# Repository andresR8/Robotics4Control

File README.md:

# Robotics4Control
A mini-sized robot for investigation in robotics and control systems
more info at: http://www.coffeebrain.org/wiki/index.php?title=Robotics_4_Control

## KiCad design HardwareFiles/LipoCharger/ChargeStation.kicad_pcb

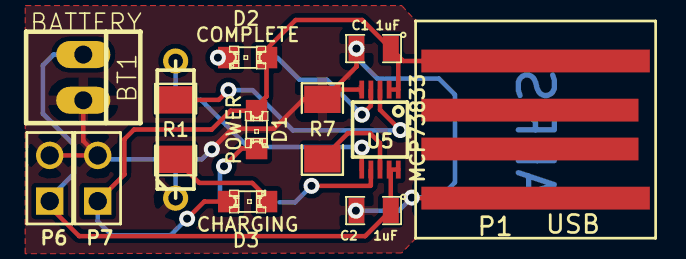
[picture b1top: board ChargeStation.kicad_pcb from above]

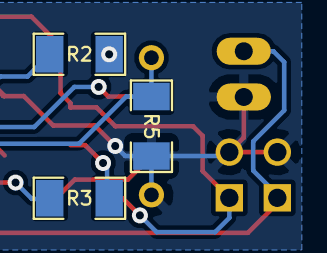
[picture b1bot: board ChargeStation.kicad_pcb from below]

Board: 2 copper layers, 16 parts (3 on the bottom side), 11 nets.

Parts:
BT1: BATTERY; PINHEAD1-2
C1, C2: 1uF; SM0805
D1: POWER; LED-0805
D2: COMPLETE; LED-0805
D3: CHARGING; LED-0805
P1: USB; USB_A_SMD
P6: BATT; PIN_ARRAY_2X1
P7: POWER; PIN_ARRAY_2X1
R1, R2, R3: 470; SM1206
R5: 5K; SM1206
R7: 10K; SM1206
R8: R3
U5: MCP73833; MSOP10-0.5

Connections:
/PROG: R5.2, R8.2, U5.6
GND: BT1.2, C1.2, C2.2, P1.4, P6.2, P7.2, R5.1, R7.1, R8.1, U5.5
unnamed: D2.2, R2.1
unnamed: D1.2, R3.1
unnamed: D3.2, R1.1
unnamed: R3.2, U5.7
unnamed: R1.2, U5.3
unnamed: R2.2, U5.4
unnamed: R7.2, U5.8
unnamed: BT1.1, C2.1, P6.1, U5.9, U5.10
VCC: C1.1, D1.1, D2.1, D3.1, P1.1, P7.1, U5.1, U5.2

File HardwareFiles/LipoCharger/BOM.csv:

Id;Designator;Package;Quantity;Designation;Manufacturer;Manufacturer ID;Mouser ID;Digikey ID
1;R2,R1,R3;SM1206;3;470;Yageo;RC1206FR-07470RL;603-RC1206FR-07470RL;311-470FRCT-ND
2;R5;SM1206;1;5K;Vishay / Dale;ESR18EZPF502;71-CRCW1206-47.5K-E3;541-47.5KFCT-ND
3;R7;SM1206;1;10K;ROHM Semiconductor;CRCW120647K5FKEA;755-ESR18EZPF1002;RHM10.0KAFTR-ND
4;C1,C2;SM0805;2;1uF;Vishay / Vitramon;VJ0805Y105KXQTW1BC;71-CRCW1206-47.5K-E3;490-1691-1-ND
5;BT1;PINHEAD1-2;1;BATTERY;TE Connectivity AMP Connectors;640456-2;"571-6404562
";A1921-ND
6;P6;PIN_ARRAY_2X1;1;BATT;TE Connectivity AMP Connectors;640456-2;"571-6404562
";A1921-ND
7;U5;MSOP10-0.5;1;MCP73833;Microchip;MCP73833-AMI/UN;579-MCP73833-AMI/UN;MCP73833-AMI/UN-ND
8;D1;LED-0805;1;POWER;Kingbright;AP2012EC;604-AP2012EC;AP2012EC-ND
9;D2;LED-0805;1;COMPLETE;Kingbright;AP2012EC;604-AP2012EC;AP2012EC-ND
10;D3;LED-0805;1;CHARGING;Kingbright;AP2012EC;604-AP2012EC;AP2012EC-ND
11;P7;PIN_ARRAY_2X1;1;POWER;TE Connectivity AMP Connectors;640456-2;"571-6404562
";A1921-ND

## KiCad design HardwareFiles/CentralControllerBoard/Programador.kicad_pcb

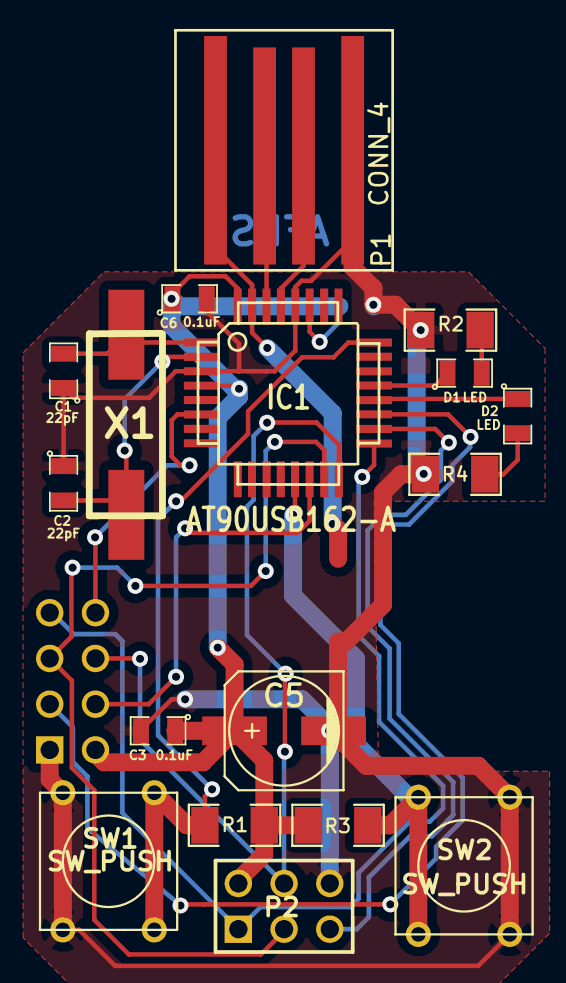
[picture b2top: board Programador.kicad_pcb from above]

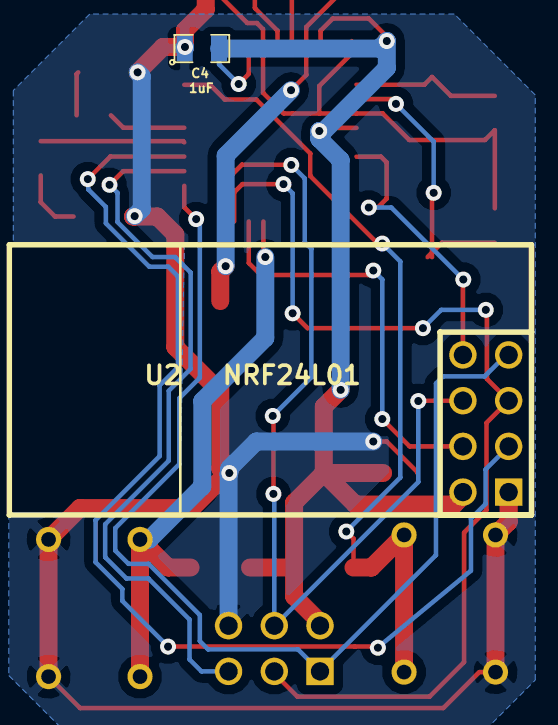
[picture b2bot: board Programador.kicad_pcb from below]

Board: 2 copper layers, 19 parts (2 on the bottom side), 20 nets.

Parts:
C1, C2: 22pF; SM0805
C3, C6: 0.1uF; SM0805
C4: 1uF; SM0805
C5: 10uF; c_elec_6.3x5.3
D1, D2: LED; SM0805
IC1: AT90USB162-A; TQFP32
P1: CONN_4; USB_A_SMD
P2: CONN_3X2; pin_array_3x2
R1, R3: 10k; SM1206
R2, R4: 430; SM1206
SW1, SW2: SW_PUSH; SW_PUSH_SMALL
U2   NRF24L01: NRF24L01; Nrf24l01
X1: crystals

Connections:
+5V: IC1.31, P1.1
/CE: IC1.19, U2 NRF24L01.3
/D+: IC1.29, P1.3
/D-: IC1.30, P1.2
/INT0: IC1.6, U2 NRF24L01.8
/MISO: IC1.17, P2.1, U2 NRF24L01.7
/MOSI: IC1.16, P2.4, U2 NRF24L01.6
/SCK: IC1.15, P2.3, U2 NRF24L01.5
/TARGET_RESET: IC1.18, P2.5
/~SS: IC1.14, U2 NRF24L01.4
GND: C1.1, C2.1, C3.2, C4.1, C5.2, C6.2, IC1.3, IC1.28, P1.4, P2.6, R2.2, R4.2, SW1.1, SW2.2, U2 NRF24L01.1
unnamed: D2.2, R4.1
unnamed: D2.1, IC1.20
unnamed: C2.2, IC1.2, X1.1
unnamed: C1.2, IC1.1, X1.2
unnamed: D1.2, R2.1
unnamed: D1.1, IC1.21
unnamed: IC1.24, R1.2, SW1.2
unnamed: IC1.13, R3.2, SW2.1
VCC: C3.1, C4.2, C5.1, C6.1, IC1.4, IC1.27, IC1.32, P2.2, R1.1, R3.1, U2 NRF24L01.2

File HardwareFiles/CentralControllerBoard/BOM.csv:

Id;Designator;Package;Quantity;Designation;Manufacturer;Manufacturer ID;Mouser ID;Digikey ID
1;IC1;TQFP32;1;AT90USB162-A;Atmel;AT90USB162-16AU;556-A90USB162-16AU;AT90USB162-16AU-ND
2;SW2,SW1;SW_PUSH_SMALL;2;SW_PUSH;TE Connectivity;FSM4JH;506-FSM4JH;450-1650-ND
3;R1,R3;SM1206;2;10K;ROHM Semiconductor;ESR18EZPF1002;755-ESR18EZPF1002;RHM10.0KAFTR-ND
4;R2,R4;SM1206;2;430;Yageo;RC1206JR-07430RL;603-RC1206JR-07430RL;311-430ERCT-ND
5;C2,C1;SM0805;2;22pF;Wurth Electronics;8.85012E+11;710-885012007012;732-7816-1-ND
6;D1,D2;SM0805;2;LED;Kingbright;AP2012EC;604-AP2012EC;AP2012EC-ND
7;C6,C3;SM0805;2;0.1uF;Yageo;CC0805ZRY5V9BB104;603-CC805ZRY5V9BB104;311-1361-1-ND
8;C4;SM0805;1;1uF;Vishay / Vitramon;VJ0805Y105KXQTW1BC;77-VJ0805Y105KXQTBC;490-1691-1-ND
9;P2;pin_array_3x2;1;CONN_3X2;Sullins Connector Solutions;PPTC032LFBN-RC;571-215309-3;
10;U2   NRF24L01;Nrf24l01;1;NRF24L01;NRF24L01;Nordic Semiconductor;http://amzn.com/B00O9O868G;
11;X1;crystals;1;16MHz;ECS Inc.;ECS-160-20-5PX-TR;520-CSM1600-20-X;XC1282CT-ND
12;C5;c_elec_6.3x5.3;1;10uF;Wurth Electronics Inc;8.75E+11;710-875105240001;732-6401-1-ND

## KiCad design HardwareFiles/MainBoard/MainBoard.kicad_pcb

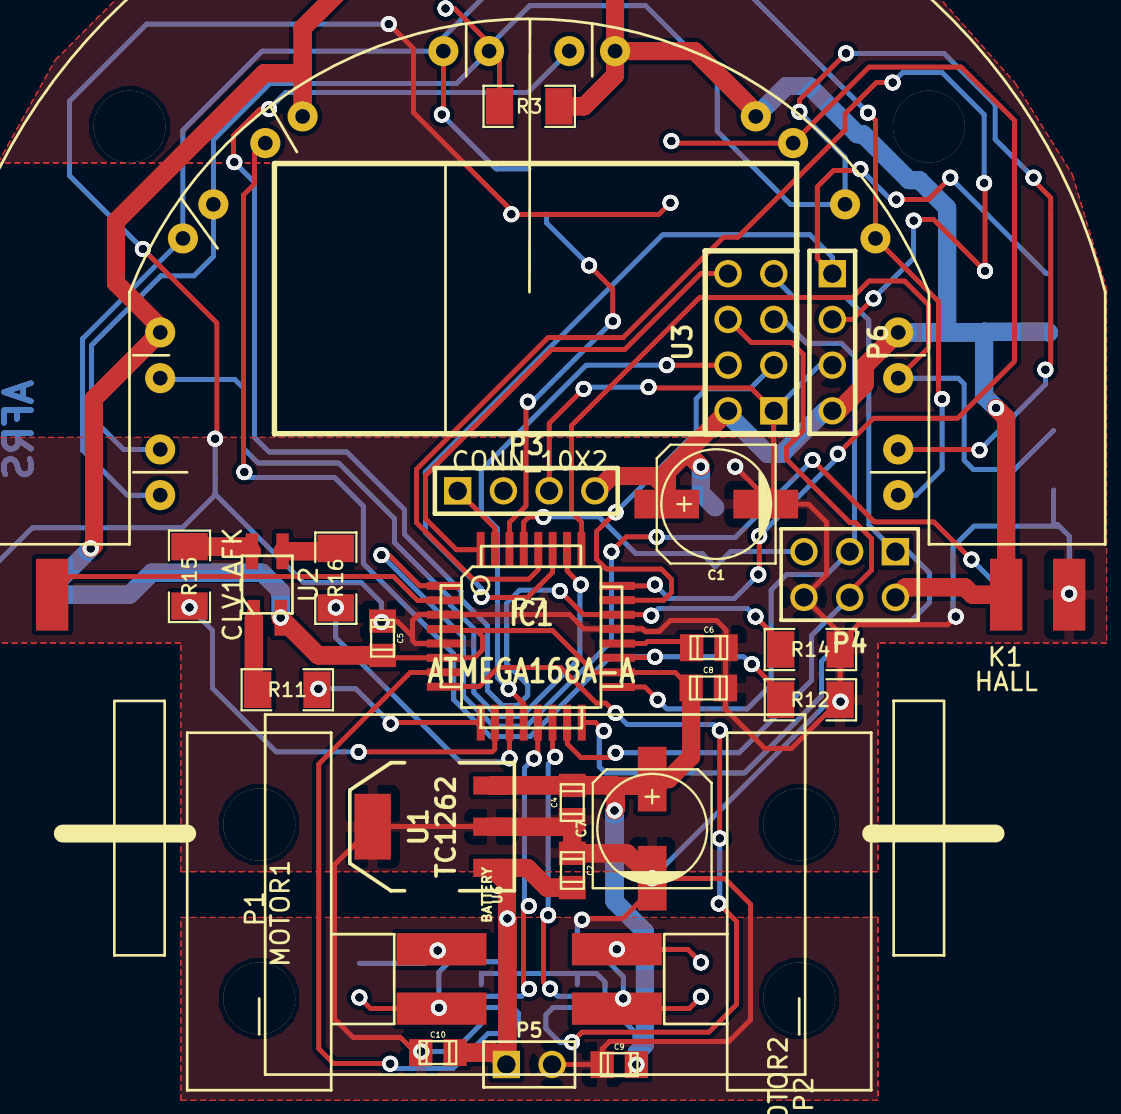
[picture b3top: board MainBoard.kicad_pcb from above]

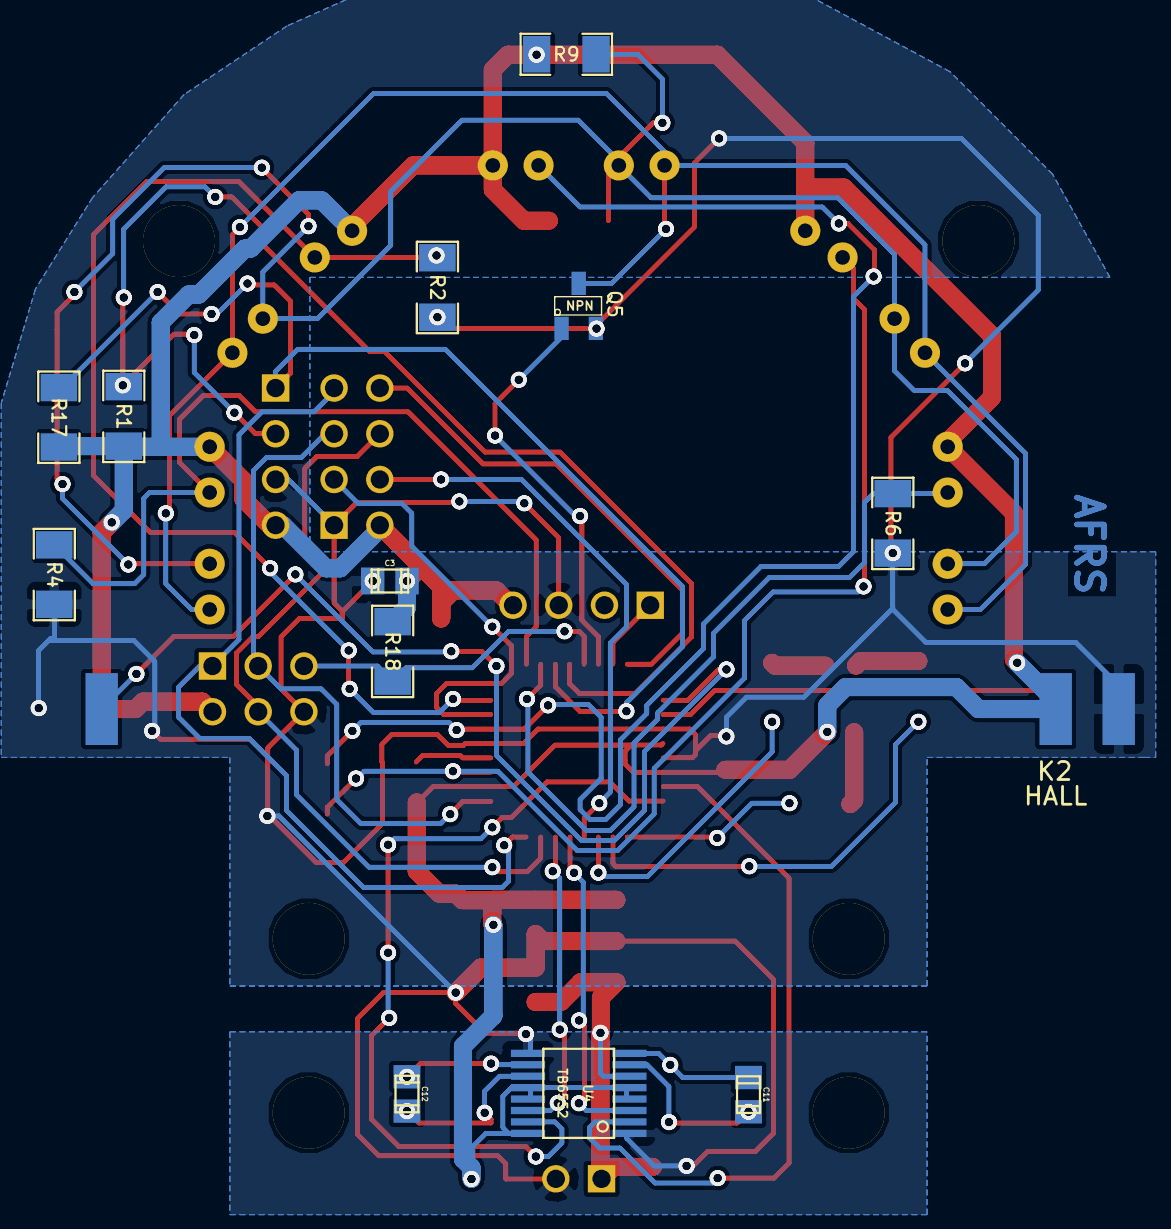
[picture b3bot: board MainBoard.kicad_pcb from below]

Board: 2 copper layers, 41 parts (13 on the bottom side), 38 nets.

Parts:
C1, C7: 10uF; c_elec_6.3x5.3
C2, C4: 1uF; c_0805
C3, C5, C8, C9, C10, C11, C12: 0.1uF; c_0805
C6: 100nF; c_0805
IC1: ATMEGA168A-A; TQFP32
K1, K2: HALL
P1: MOTOR1; MotorLeft
P2: MOTOR2; MotorRight
P3: BT; PIN_ARRAY_4x1
P4: AVRSPI; pin_array_3x2
P5: BATT; PIN_ARRAY_2X1
P6: I2C; PIN_ARRAY_4x1
P7: CONN_10X2; IR_Sensors
Q5: NPN; SOT23_MOD
R1, R17, R18: 10K; SM1206
R2, R4, R6, R12, R14: 1.5K; SM1206
R3, R9: 33; SM1206
R11, R15, R16: 430; SM1206
U1: TC1262; SOT223
U2: CLV1AFK; LEDRGB
U3: NRF24L01; Nrf24l01
U4: TB6552; ssop_16
U6: BATTERY; Battery3x2

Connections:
+3.3V: C1.1, C3.1, C4.1, C5.1, C7.1, C8.2, C9.1, IC1.4, IC1.6, IC1.18, K1.1, K2.1, P3.4, P4.2, P6.4, P7.2, P7.4, P7.6, P7.8, P7.10, R1.2, R3.1, R9.1, R17.2, R18.1, U1.3, U2.2, U3.2, U4.4, U4.5, U4.12, U4.13, U4.16
/ADC1: IC1.24, P7.1, R2.1
/ADC2: IC1.25, P7.3, R4.1
/ADC3: IC1.26, P7.5, R6.1
/ADC6: IC1.19, P7.7, R12.1
/ADC7: IC1.22, P7.9, R14.2
/AO1: C11.1, P1.2, U4.7
/AO2: C11.2, P1.1, U4.8
/BLUE: IC1.11, R16.2
/BO1: C12.1, P2.2, U4.11
/BO2: C12.2, P2.1, U4.10
/CE: IC1.23, U3.3
/GREEN: IC1.10, R15.2
/INT0: IC1.32, U3.8
/M1: IC1.7, U4.2
/M2: IC1.8, U4.15
/MISO: IC1.16, P4.1, U3.7
/MOSI: IC1.15, P4.4, U3.6
/OC1A: IC1.13, U4.3
/OC1B: IC1.14, U4.14
/PCINT19: IC1.1, K1.3
/PCINT20: IC1.2, K2.3
/PD0: IC1.30, Q5.1
/RED: IC1.9, R11.1
/RESET: IC1.29, P4.5, R18.2
/SCK: IC1.17, P4.3, U3.5
/SCL: IC1.28, P6.2, R1.1
/SDA: IC1.27, P6.1, R17.1
/TX: IC1.31, P3.1
/~SS: IC1.12, U3.4
AGND: C1.2, C2.2, C3.2, C4.2, C5.2, C6.1, C7.2, C8.1, C9.2, C10.2, IC1.3, IC1.5, IC1.21, K1.2, K2.2, P3.3, P4.6, P5.2, P6.3, Q5.2, R2.2, R4.2, R6.2, R12.2, R14.1, U1.2, U1.4, U3.1, U4.1, U4.9
unnamed: P7.11, P7.13, P7.15, P7.17, P7.19, Q5.3
unnamed: P7.12, P7.14, P7.16, P7.18, P7.20, R3.2, R9.2
unnamed: R11.2, U2.1
unnamed: R16.1, U2.3
unnamed: R15.1, U2.4
unnamed: C6.2, IC1.20
VCC: C2.1, C10.1, P5.1, U1.1, U4.6

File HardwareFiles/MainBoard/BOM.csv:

Id;Designator;Package;Quantity;Designation;Manufacturer;Manufacturer Part Number;Mouser Part Number;Digikey Part Number
1;P7;IR_Sensors;5;CONN_10X2; Osram Opto Semiconductor;SFH 4545;720-SFH4545;475-2919-ND
1;P8;IR_Sensors/ Phototransistors;5;CONN_10X2;Vishay Semiconductors ;TEFT4300;782-TEFT4300;751-1041-ND
3;Q5;SOT23_MOD;1;NPN;ON Semiconductor;MMBT3904LT3G;863-MMBT2222ALT1G;MMBT2222ALT1GOSCT-ND
4;U4;ssop_16;1;TB6552;Toshiba;TB6552;757-TB6552FNGC8EL;TB6552FNGC8ELCT-ND
5;U2;LEDRGB;1;CLV1AFK;Cree, Inc.;CLV1A-FKB-CHMKPEHBB7A363;941-V1AFKBCHMKPEH7A3;CLV1A-FKB-CK1N1G1BB7R4S3CT-ND
6;R3,R9;SM1206;2;33;ROHM Semiconductor;ESR18EZPJ330;755-ESR18EZPJ330;RHM33ITR-ND
7;R18,R1,R17;SM1206;3;10K;ROHM Semiconductor;ESR18EZPF1002;755-ESR18EZPF1002;RHM10.0KAFTR-ND
8;IC1;TQFP32;1;ATMEGA168A-A;Atmel;ATMEGA168A-AU;556-ATMEGA168A-AU;ATMEGA168A-AU-ND
9;C2,C4;c_0805;2;1uF;Vishay / Vitramon;VJ0805Y105KXQTW1BC;77-VJ0805Y105KXQTBC;490-1691-1-ND
10;C8,C9,C10,C5,C12,C3,C11,C6;c_0805;7;0.1uF;Yageo;CC0805ZRY5V9BB104;603-CC805ZRY5V9BB104;311-1361-1-ND
12;C1,C7;c_elec_6.3x5.3;2;10uF;Wurth Electronics Inc;875105240001;710-875105240001;732-6401-1-ND
13;P1,P2;Motor;2;MOTOR1,MOTOR2;;;;
14;P5;PIN_ARRAY_2X1;1;BATT;;;;
15;P4;pin_array_3x2;1;AVRSPI;Sullins Connector Solutions;PPTC032LFBN-RC;571-215309-3;S7071-ND
16;P3;PIN_ARRAY_4x1;1;BT;Harwin Inc.;M20-7820446;855-M20-7820446;952-1792-ND
17;R2,R4,R12,R14,R6;SM1206;5;1.5K;Yageo;RC1206JR-071K5L;603-RC1206JR-071K5L;311-1.5KERCT-ND
18;R11,R15,R16;SM1206;3;430;Yageo;RC1206FR-07430RL;603-RC1206FR-07430RL;311-430FRCT-ND
19;U1;SOT223;1;TC1262;Microchip Technology;TC1262-3.3VDBTR;579-TC1262-3.3VDBTR;TC1262-3.3VDBCT-ND
21;U3;Nrf24l01;1;NRF24L01;Nordic Semiconductor;;http://amzn.com/B00O9O868G;
22;P6;PIN_ARRAY_4x1;1;I2C;Harwin Inc.;M20-7820446;855-M20-7820446;952-1792-ND

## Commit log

2016-05-07 3D Printed parts
2016-05-07 Central Controller electronic board design
2016-05-07 Lipo Charger electronic board design
2016-05-07 Robot Main Board design
2016-05-07 Robot Software sketch
2016-05-07 AVRISP MKII Programmer
2016-05-07 USB to NRFL24L01 Project
2016-05-07 Debug Files
2016-05-07 LUFAConfig files
2016-05-07 LUFA core files
2016-05-07 USB LUFA Drivers
2016-05-07 Central Controller java UI
2016-05-07 Project link
2016-08-24 BOM file added
2016-08-24 new kicad board format
2016-08-24 Remove legacy kicad file
2016-08-24 gerber files updated
2016-08-24 Schematic File added
2016-08-24 BOM file completed
2016-08-26 Board & Schematic File added
2016-08-26 Kicad design files added
2016-08-26 typo fixed

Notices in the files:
HardwareFiles/CentralControllerBoard/Programador.kicad_pcb:
http://creativecommons.org/licenses/by-nc-sa/4.0/)
Creative Commons Attribution-NonCommercial-ShareAlike 4.0 International License
This work is licensed under a:
